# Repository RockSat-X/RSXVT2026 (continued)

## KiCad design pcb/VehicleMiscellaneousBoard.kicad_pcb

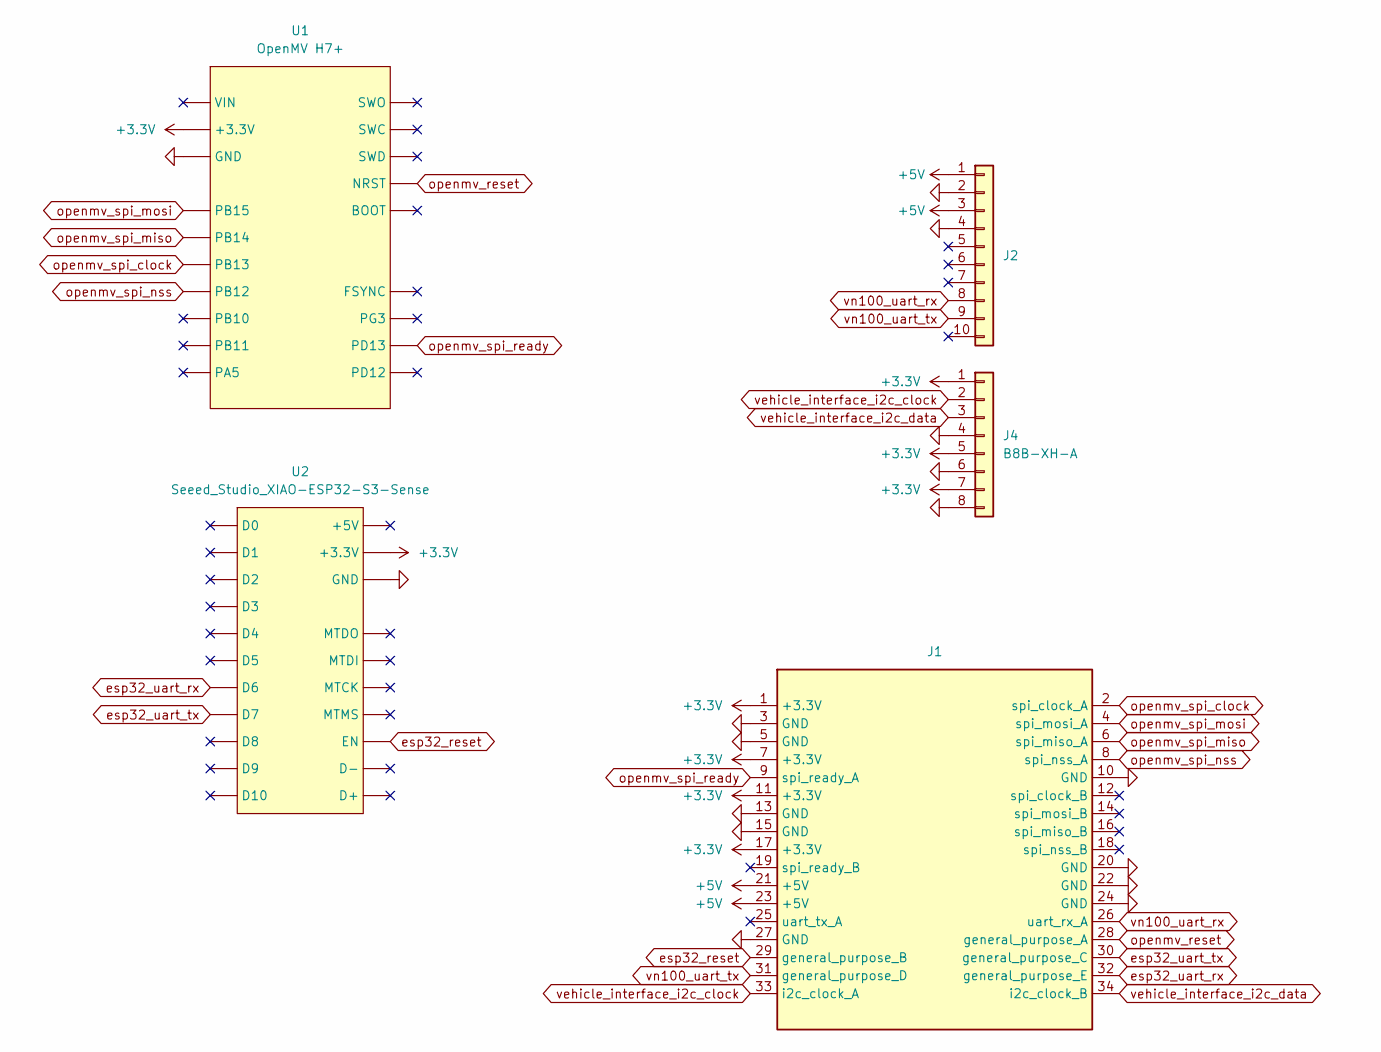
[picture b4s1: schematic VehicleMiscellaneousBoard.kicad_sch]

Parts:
J1: VehicleStackConnector
J2: Conn_02x05_Top_Bottom; JST_XH_S10B-XH-A_1x10_P2.50mm_Horizontal
J4: B8B-XH-A; JST_XH_B8B-XH-A_1x08_P2.50mm_Vertical
U1: OpenMV H7+; OpenMV_H7_Plus
U2: Seeed_Studio_XIAO-ESP32-S3-Sense; Seeed_Studio_XIAO_ESP32_S3

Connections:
+3.3V: J1.1 (+3.3V), J1.7 (+3.3V), J1.11 (+3.3V), J1.17 (+3.3V), J4.1, J4.5, J4.7, U1.+3.3V, U2.+3.3V
+5V: J1.21 (+5V), J1.23 (+5V), J2.1, J2.3
GND: J1.3 (GND), J1.5 (GND), J1.10 (GND), J1.13 (GND), J1.15 (GND), J1.20 (GND), J1.22 (GND), J1.24 (GND), J1.27 (GND), J2.2, J2.4, J4.4, J4.6, J4.8, U1.GND, U2.GND
esp32_reset: J1.29 (general_purpose_B), U2.EN
esp32_uart_rx: J1.32 (general_purpose_E), U2.D6
esp32_uart_tx: J1.30 (general_purpose_C), U2.D7
openmv_reset: J1.28 (general_purpose_A), U1.NRST
openmv_spi_clock: J1.2 (spi_clock_A), U1.PB13
openmv_spi_miso: J1.6 (spi_miso_A), U1.PB14
openmv_spi_mosi: J1.4 (spi_mosi_A), U1.PB15
openmv_spi_nss: J1.8 (spi_nss_A), U1.PB12
openmv_spi_ready: J1.9 (spi_ready_A), U1.PD13
vehicle_interface_i2c_clock: J1.33 (i2c_clock_A), J4.2
vehicle_interface_i2c_data: J1.34 (i2c_clock_B), J4.3
vn100_uart_rx: J1.26 (uart_rx_A), J2.8
vn100_uart_tx: J1.31 (general_purpose_D), J2.9

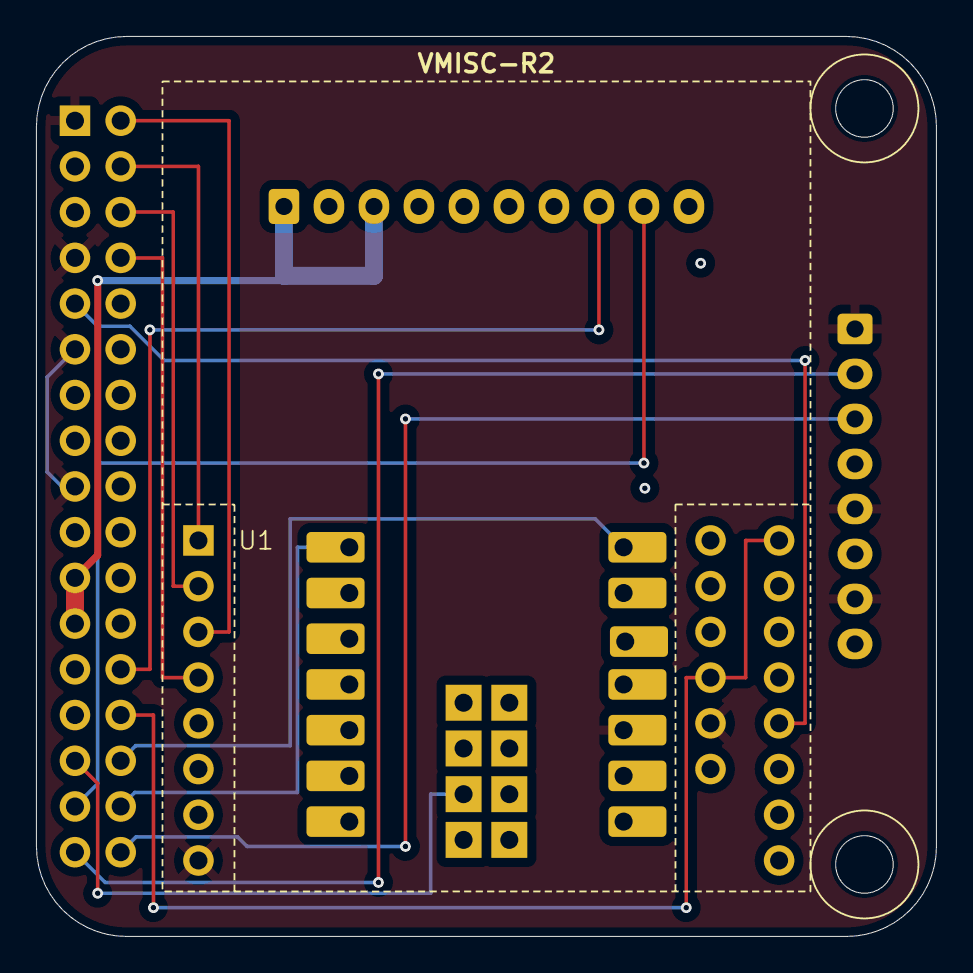
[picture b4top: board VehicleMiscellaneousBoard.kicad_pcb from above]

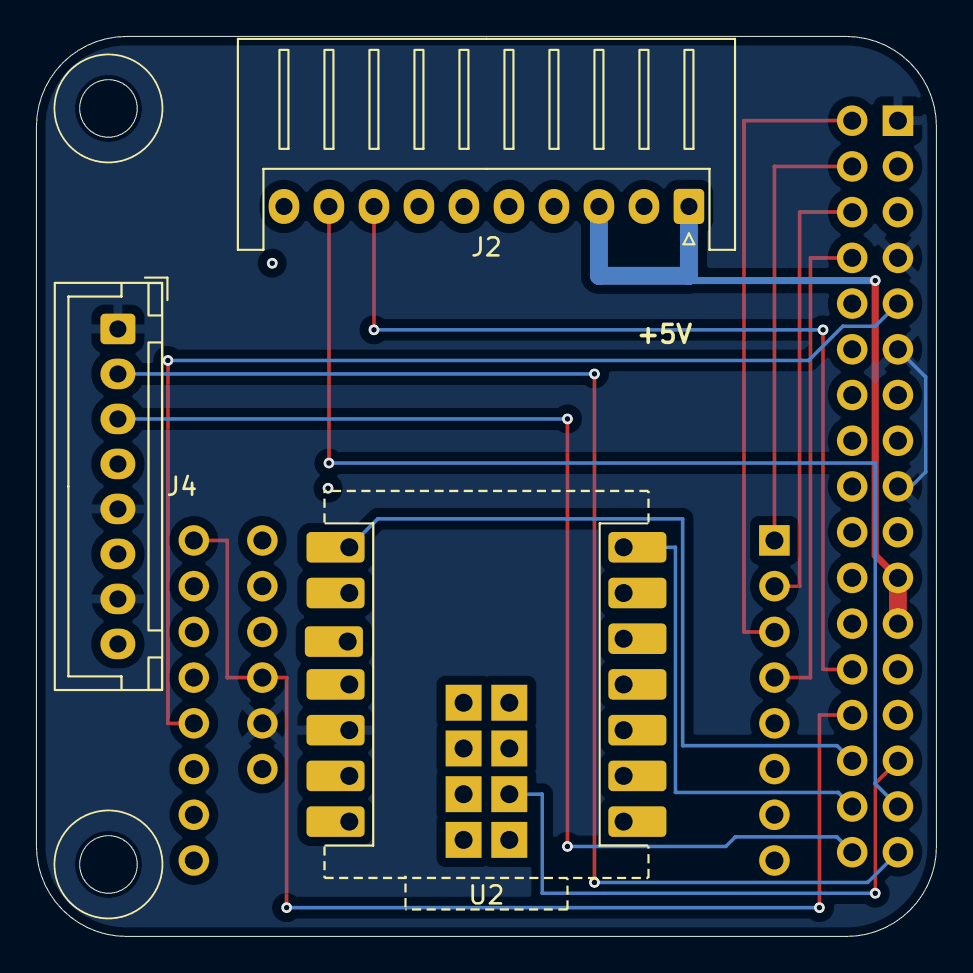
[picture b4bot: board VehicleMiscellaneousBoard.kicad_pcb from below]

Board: 4 copper layers, 50.0 x 50.0 mm, 6 parts (3 on the bottom side), 16 nets.

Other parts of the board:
N1: Housing; Dummy

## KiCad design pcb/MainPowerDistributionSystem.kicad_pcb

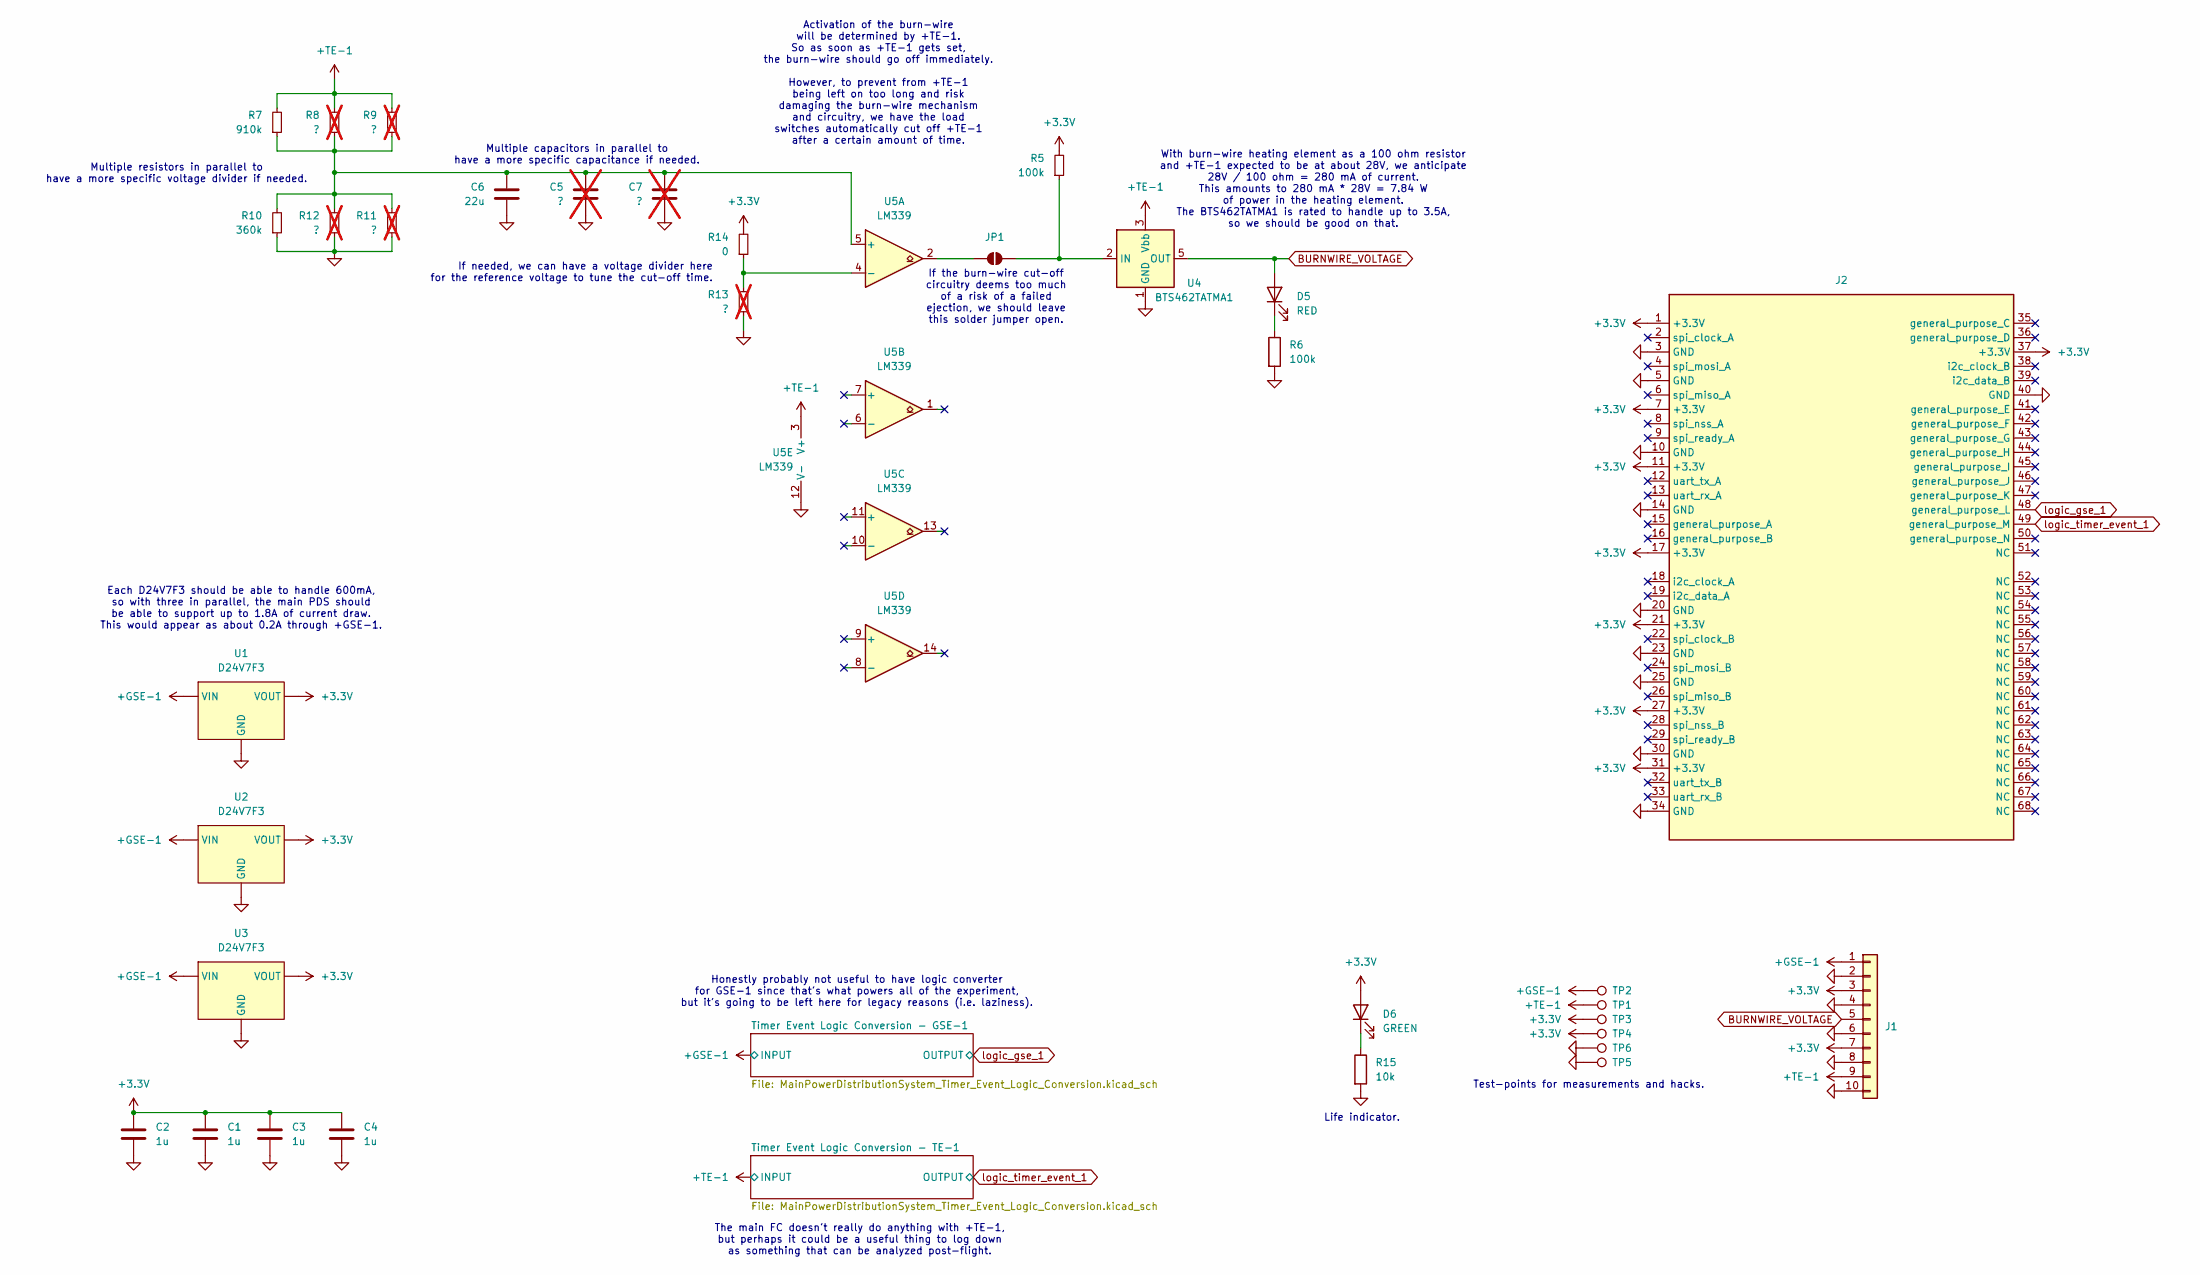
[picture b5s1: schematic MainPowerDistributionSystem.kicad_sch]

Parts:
C1, C2, C3, C4: 1u; C_1206_3216Metric_Pad1.33x1.80mm_HandSolder
C5, C7: ?; C_1206_3216Metric_Pad1.33x1.80mm_HandSolder; not fitted
C6: 22u; C_1206_3216Metric_Pad1.33x1.80mm_HandSolder
D5: RED; LED_1206_3216Metric_Pad1.42x1.75mm_HandSolder
D6: GREEN; LED_1206_3216Metric_Pad1.42x1.75mm_HandSolder
J1: Conn_02x05_Top_Bottom; JST_XH_S10B-XH-A_1x10_P2.50mm_Horizontal
J2: MainStackConnector
JP1: SolderJumper_2_Open; SolderJumper-2_P1.3mm_Open_RoundedPad1.0x1.5mm
R5, R6: 100k; R_1206_3216Metric_Pad1.30x1.75mm_HandSolder
R7: 910k; R_1206_3216Metric_Pad1.30x1.75mm_HandSolder
R8, R9, R11, R12, R13: ?; R_1206_3216Metric_Pad1.30x1.75mm_HandSolder; not fitted
R10: 360k; R_1206_3216Metric_Pad1.30x1.75mm_HandSolder
R14: 0; R_1206_3216Metric_Pad1.30x1.75mm_HandSolder
R15: 10k; R_1206_3216Metric_Pad1.30x1.75mm_HandSolder
TP1, TP2, TP3, TP4, TP5, TP6: TestPoint; TestPoint_Bridge_Pitch2.0mm_Drill0.7mm
U1, U2, U3: D24V7F3; D24V7Fx
U4: BTS462TATMA1; TO-252-4
U5: LM339; SOIC-14_3.9x8.7mm_P1.27mm

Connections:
+3.3V: C1.1, C2.1, C3.1, C4.1, D6.2 (A), J1.3, J1.7, J2.1 (+3.3V), J2.7 (+3.3V), J2.11 (+3.3V), J2.17 (+3.3V), J2.21 (+3.3V), J2.27 (+3.3V), J2.31 (+3.3V), J2.37 (+3.3V), R5.2, R14.2, TP3.1, TP4.1, U1.VOUT, U2.VOUT, U3.VOUT
+GSE-1: J1.1, TP2.1, U1.VIN, U2.VIN, U3.VIN; also elsewhere on the board
+TE-1: J1.9, R7.2, R8.2, R9.2, TP1.1, U4.3 (Vbb), U5.3 (V+); also elsewhere on the board
BURNWIRE_VOLTAGE: D5.2 (A), J1.5, U4.5 (OUT)
GND: C1.2, C2.2, C3.2, C4.2, C5.2, C6.2, C7.2, J1.2, J1.4, J1.6, J1.8, J1.10, J2.3 (GND), J2.5 (GND), J2.10 (GND), J2.14 (GND), J2.20 (GND), J2.23 (GND), J2.25 (GND), J2.30 (GND), J2.34 (GND), J2.40 (GND), R6.2, R10.1, R11.1, R12.1, R13.1, R15.2, TP5.1, TP6.1, U1.GND, U2.GND, U3.GND, U4.1 (GND), U5.12 (V-); also elsewhere on the board
unnamed: D5.1 (K), R6.1
unnamed: D6.1 (K), R15.1
unnamed: JP1.1 (A), U5.2
unnamed: JP1.2 (B), R5.1, U4.2 (IN)
unnamed: C5.1, C6.1, C7.1, R7.1, R8.1, R9.1, R10.2, R11.2, R12.2, U5.5 (+)
unnamed: R13.2, R14.1, U5.4 (-)
logic_gse_1: J2.48 (general_purpose_L); also elsewhere on the board
logic_timer_event_1: J2.49 (general_purpose_M); also elsewhere on the board

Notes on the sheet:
Multiple resistors in parallel to have a more specific voltage divider if needed.
Activation of the burn-wire will be determined by +TE-1. So as soon as +TE-1 gets set, the burn-wire should go off immediately. However, to prevent from +TE-1 being left on too long and risk damaging the burn-wire mechanism and circuitry, we have the load switches automatically cut off +TE-1 after 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
With burn-wire heating element as a 100 ohm resistor and +TE-1 expected to be at about 28V, we anticipate 28V / 100 ohm = 280 mA of current. This amounts to 280 mA * 28V = 7.84 W of power in the heating element. The BTS462TATMA1 is rated to handle up to 3.5A, so we should be good on that.
Multiple capacitors in parallel to have a more specific capacitance if needed.
If the burn-wire cut-off circuitry deems too much of a risk of a failed ejection, we should leave this solder jumper open.
Life indicator.
Honestly probably not useful to have logic converter for GSE-1 since that's what powers all of the experiment, but it's going to be left here for legacy reasons (i.e. laziness).
The main FC doesn't really do anything with +TE-1, but perhaps it could be a useful thing to log down as something that can be analyzed post-flight.
If needed, we can have a voltage divider here for the reference voltage to tune the cut-off time.
Test-points for measurements and hacks.
Each D24V7F3 should be able to handle 600mA, so with three in parallel, the main PDS should be able to support up to 1.8A of current draw. This would appear as about 0.2A through +GSE-1.

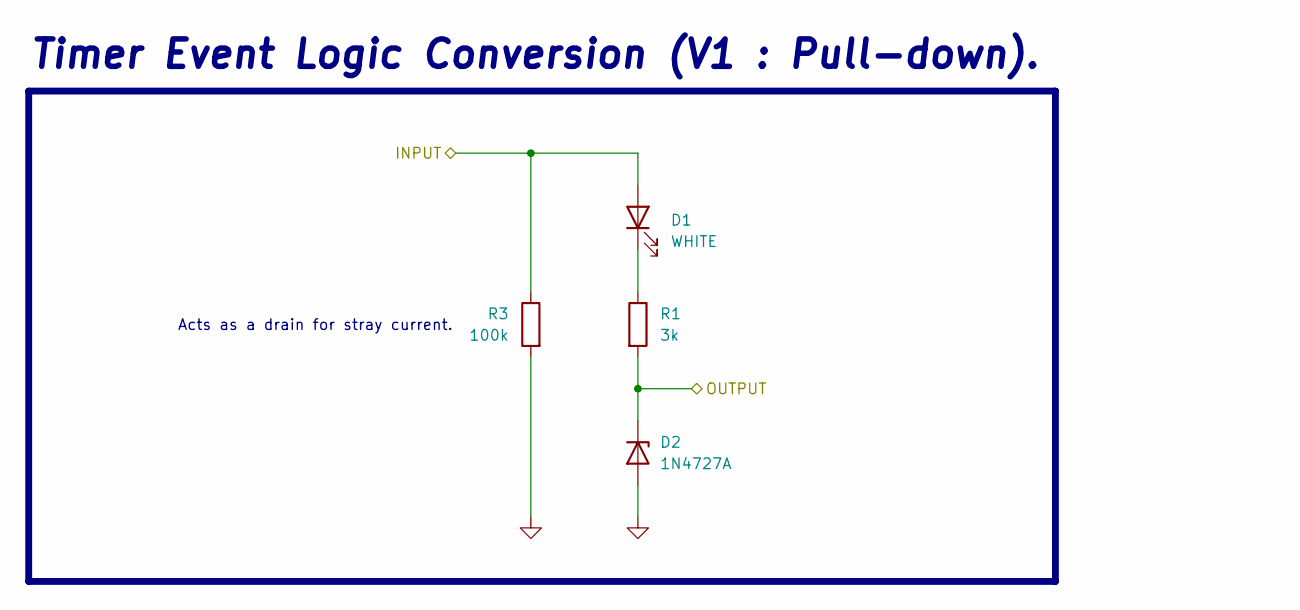
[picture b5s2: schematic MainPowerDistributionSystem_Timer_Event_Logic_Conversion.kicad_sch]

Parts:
D1: WHITE; LED_1206_3216Metric_Pad1.42x1.75mm_HandSolder
D2: 1N4727A; D_A-405_P7.62mm_Horizontal
R1: 3k; R_1206_3216Metric_Pad1.30x1.75mm_HandSolder
R3: 100k; R_1206_3216Metric_Pad1.30x1.75mm_HandSolder

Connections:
+TE-1: D1.2 (A), R3.1; also elsewhere on the board
GND: D2.2 (A), R3.2; also elsewhere on the board
unnamed: D1.1 (K), R1.1
logic_timer_event_1: D2.1 (K), R1.2; also elsewhere on the board

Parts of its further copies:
D3: WHITE; LED_1206_3216Metric_Pad1.42x1.75mm_HandSolder
D4: 1N4727A; D_A-405_P7.62mm_Horizontal
R2: 3k; R_1206_3216Metric_Pad1.30x1.75mm_HandSolder
R4: 100k; R_1206_3216Metric_Pad1.30x1.75mm_HandSolder

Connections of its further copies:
+GSE-1: D3.2 (A), R4.1; also elsewhere on the board
GND: D4.2 (A), R4.2; also elsewhere on the board
unnamed: D3.1 (K), R2.1
logic_gse_1: D4.1 (K), R2.2; also elsewhere on the board

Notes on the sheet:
Timer Event Logic Conversion (V1 : Pull-down).
Acts as a drain for stray current.

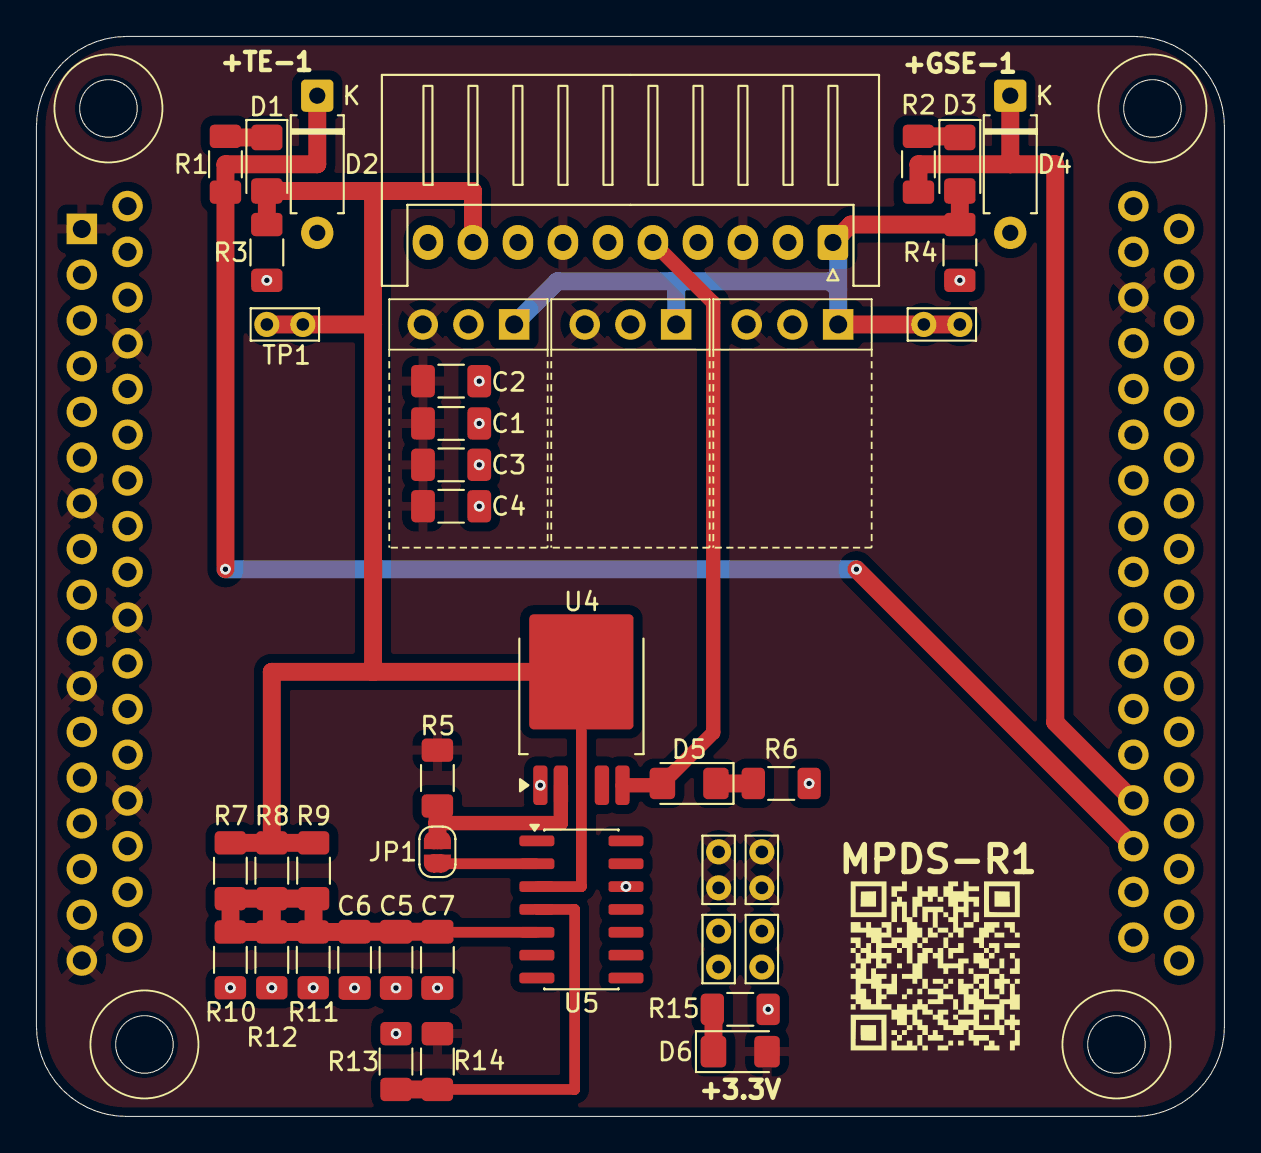
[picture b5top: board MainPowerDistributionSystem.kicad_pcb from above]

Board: 2 copper layers, 66.0 x 60.0 mm, 43 parts (0 on the bottom side), 15 nets.

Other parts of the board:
N1: Housing; MainPowerDistributionSystemHousing

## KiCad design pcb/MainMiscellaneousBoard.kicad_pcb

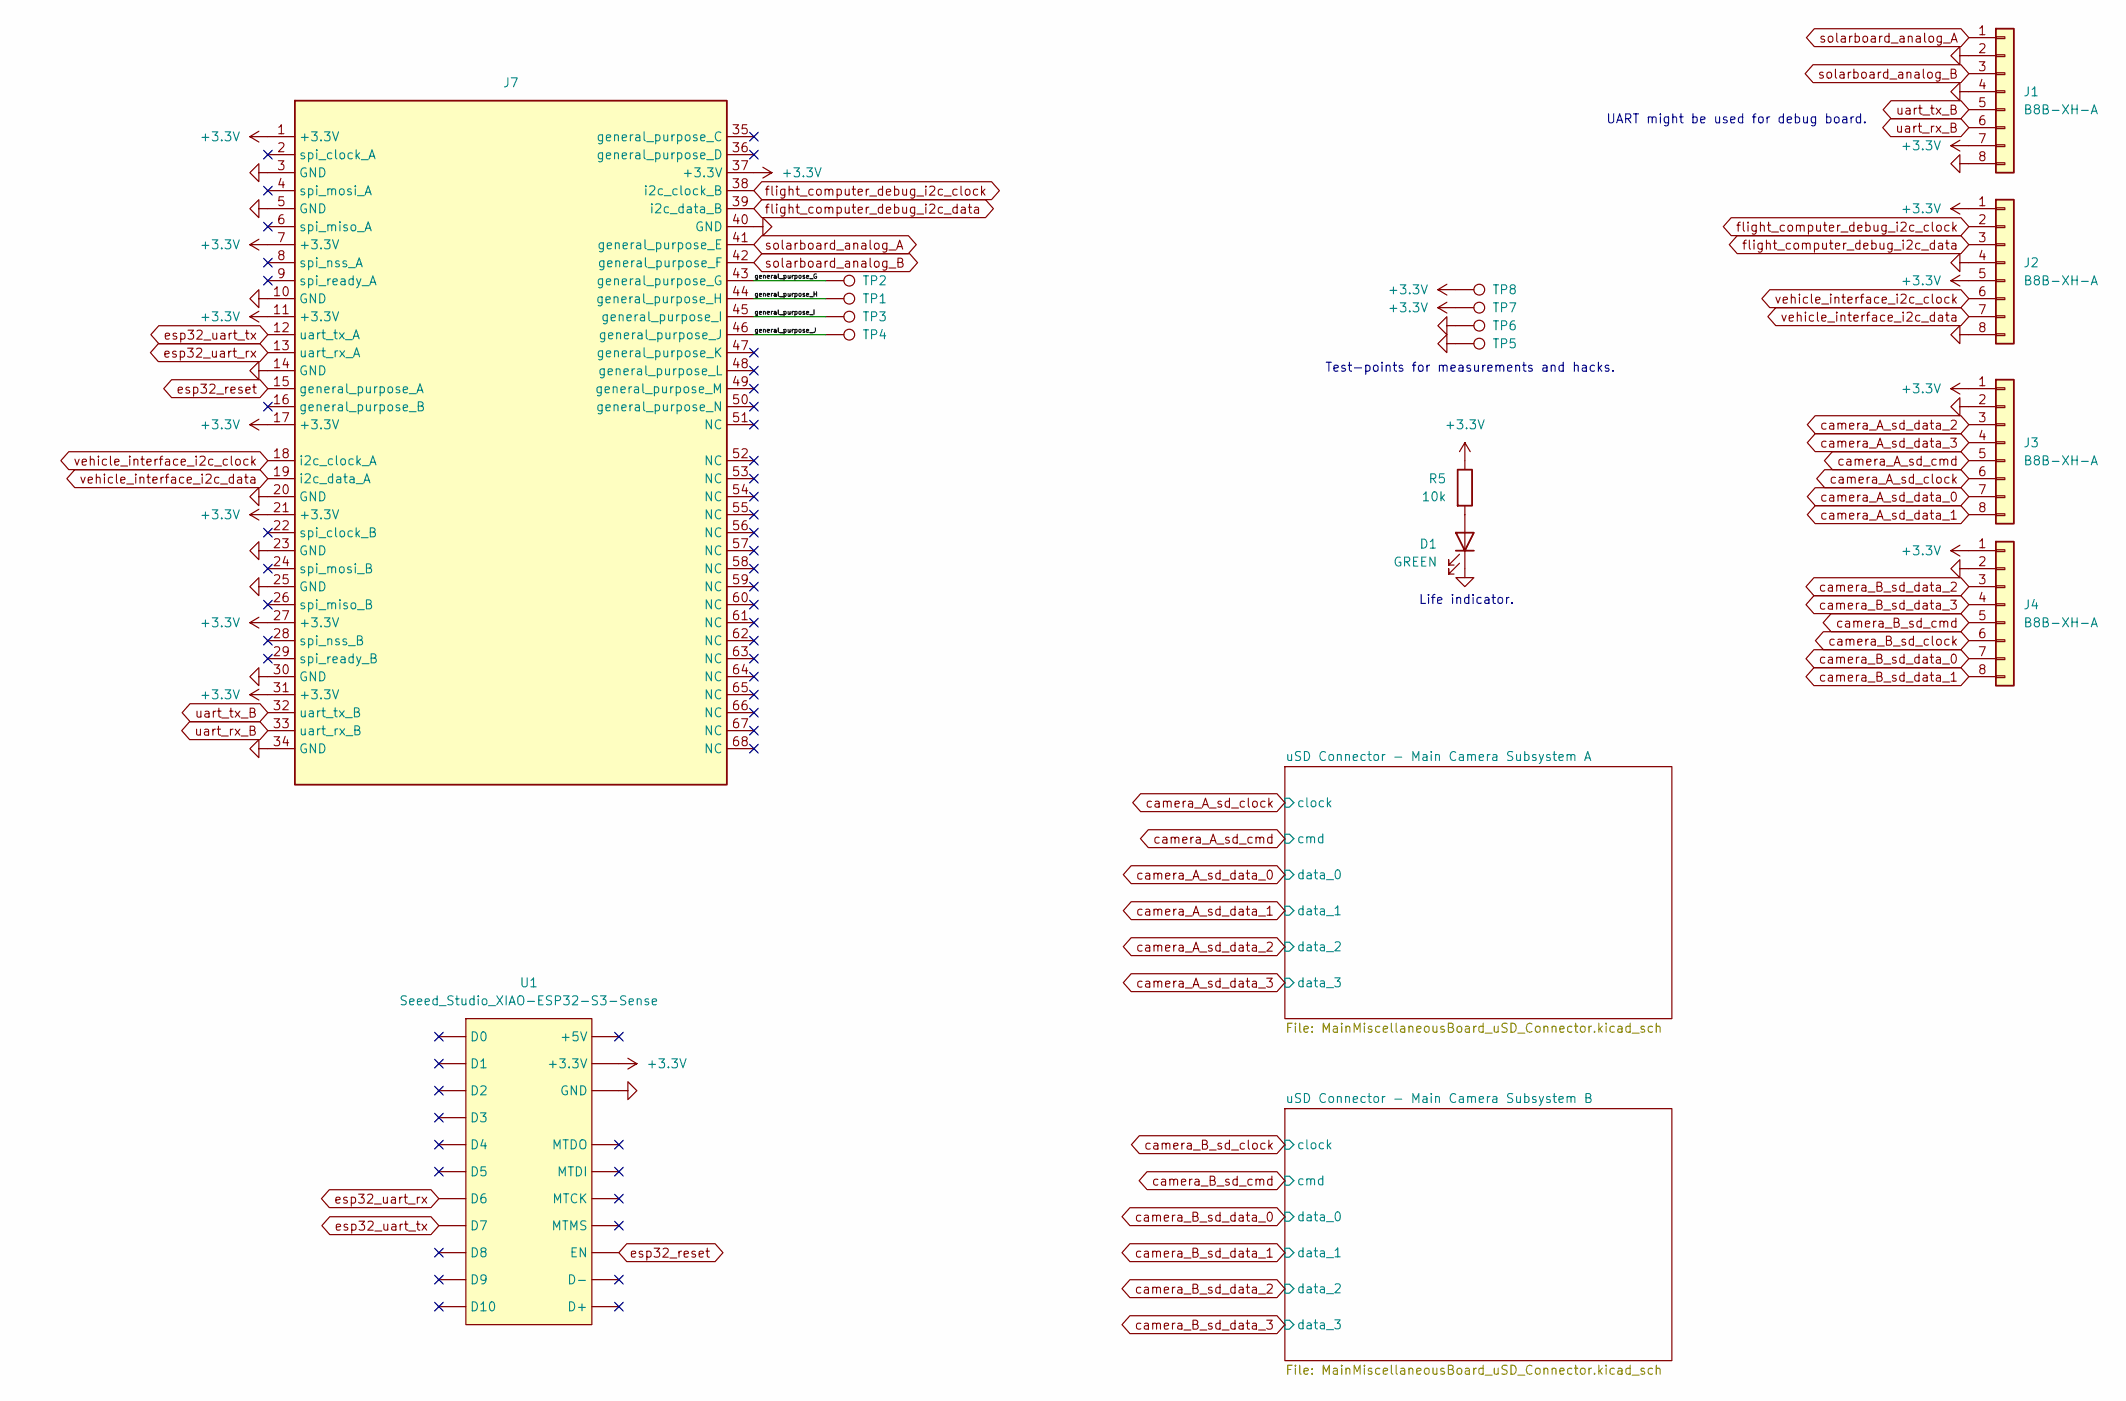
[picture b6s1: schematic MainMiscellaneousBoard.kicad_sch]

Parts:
D1: GREEN; LED_1206_3216Metric_Pad1.42x1.75mm_HandSolder
J1, J2, J3, J4: B8B-XH-A; JST_XH_B8B-XH-A_1x08_P2.50mm_Vertical
J7: MainStackConnector
R5: 10k; R_1206_3216Metric_Pad1.30x1.75mm_HandSolder
TP1, TP2, TP3, TP4, TP5, TP6, TP7, TP8: TestPoint; TestPoint_Bridge_Pitch2.0mm_Drill0.7mm
U1: Seeed_Studio_XIAO-ESP32-S3-Sense; Seeed_Studio_XIAO_ESP32_S3

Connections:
+3.3V: J1.7, J2.1, J2.5, J3.1, J4.1, J7.1 (+3.3V), J7.7 (+3.3V), J7.11 (+3.3V), J7.17 (+3.3V), J7.21 (+3.3V), J7.27 (+3.3V), J7.31 (+3.3V), J7.37 (+3.3V), R5.1, TP7.1, TP8.1, U1.+3.3V; also elsewhere on the board
/general_purpose_G: J7.43 (general_purpose_G), TP2.1
/general_purpose_H: J7.44 (general_purpose_H), TP1.1
/general_purpose_I: J7.45 (general_purpose_I), TP3.1
/general_purpose_J: J7.46 (general_purpose_J), TP4.1
GND: D1.1 (K), J1.2, J1.4, J1.8, J2.4, J2.8, J3.2, J4.2, J7.3 (GND), J7.5 (GND), J7.10 (GND), J7.14 (GND), J7.20 (GND), J7.23 (GND), J7.25 (GND), J7.30 (GND), J7.34 (GND), J7.40 (GND), TP5.1, TP6.1, U1.GND; also elsewhere on the board
unnamed: D1.2 (A), R5.2
camera_A_sd_clock: J3.6; also elsewhere on the board
camera_A_sd_cmd: J3.5; also elsewhere on the board
camera_A_sd_data_0: J3.7; also elsewhere on the board
camera_A_sd_data_1: J3.8; also elsewhere on the board
camera_A_sd_data_2: J3.3; also elsewhere on the board
camera_A_sd_data_3: J3.4; also elsewhere on the board
camera_B_sd_clock: J4.6; also elsewhere on the board
camera_B_sd_cmd: J4.5; also elsewhere on the board
camera_B_sd_data_0: J4.7; also elsewhere on the board
camera_B_sd_data_1: J4.8; also elsewhere on the board
camera_B_sd_data_2: J4.3; also elsewhere on the board
camera_B_sd_data_3: J4.4; also elsewhere on the board
esp32_reset: J7.15 (general_purpose_A), U1.EN
esp32_uart_rx: J7.13 (uart_rx_A), U1.D6
esp32_uart_tx: J7.12 (uart_tx_A), U1.D7
flight_computer_debug_i2c_clock: J2.2, J7.38 (i2c_clock_B)
flight_computer_debug_i2c_data: J2.3, J7.39 (i2c_data_B)
solarboard_analog_A: J1.1, J7.41 (general_purpose_E)
solarboard_analog_B: J1.3, J7.42 (general_purpose_F)
uart_rx_B: J1.6, J7.33 (uart_rx_B)
uart_tx_B: J1.5, J7.32 (uart_tx_B)
vehicle_interface_i2c_clock: J2.6, J7.18 (i2c_clock_A)
vehicle_interface_i2c_data: J2.7, J7.19 (i2c_data_A)

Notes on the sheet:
Test-points for measurements and hacks.
Life indicator.
UART might be used for debug board.

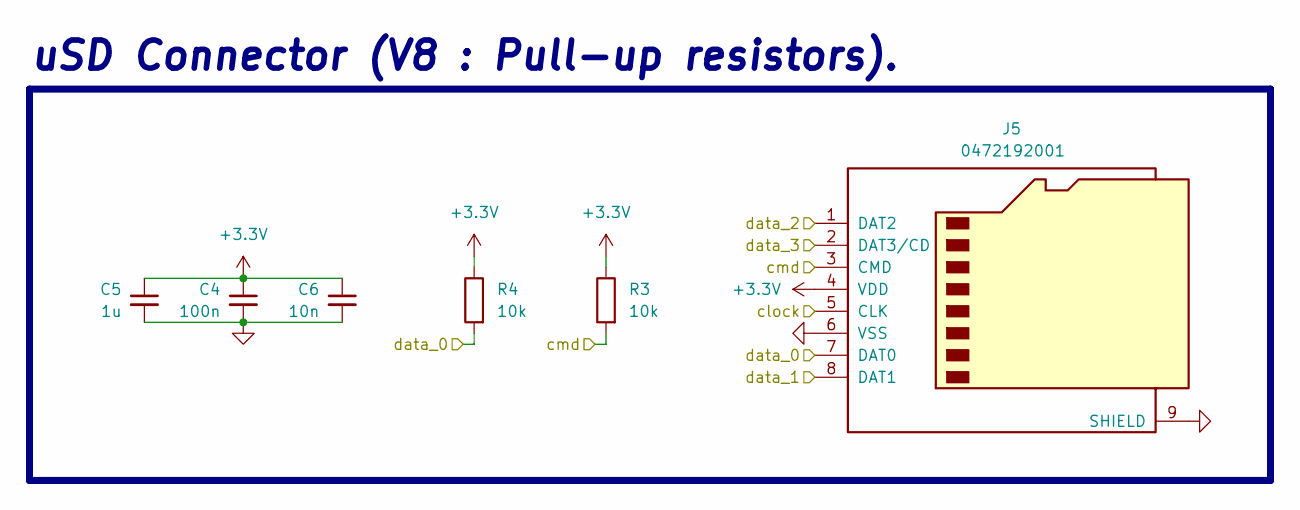
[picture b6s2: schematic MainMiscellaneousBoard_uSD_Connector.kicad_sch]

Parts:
C4: 100n; C_1206_3216Metric_Pad1.33x1.80mm_HandSolder
C5: 1u; C_1206_3216Metric_Pad1.33x1.80mm_HandSolder
C6: 10n; C_1206_3216Metric_Pad1.33x1.80mm_HandSolder
J5: 0472192001; microSD_HC_Molex_47219-2001
R3, R4: 10k; R_1206_3216Metric_Pad1.30x1.75mm_HandSolder

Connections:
+3.3V: C4.1, C5.1, C6.1, J5.4 (VDD), R3.1, R4.1; also elsewhere on the board
GND: C4.2, C5.2, C6.2, J5.6 (VSS), J5.9 (SHIELD); also elsewhere on the board
camera_A_sd_clock: J5.5 (CLK); also elsewhere on the board
camera_A_sd_cmd: J5.3 (CMD), R3.2; also elsewhere on the board
camera_A_sd_data_0: J5.7 (DAT0), R4.2; also elsewhere on the board
camera_A_sd_data_1: J5.8 (DAT1); also elsewhere on the board
camera_A_sd_data_2: J5.1 (DAT2); also elsewhere on the board
camera_A_sd_data_3: J5.2 (DAT3/CD); also elsewhere on the board

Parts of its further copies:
C1: 1u; C_1206_3216Metric_Pad1.33x1.80mm_HandSolder
C2: 100n; C_1206_3216Metric_Pad1.33x1.80mm_HandSolder
C3: 10n; C_1206_3216Metric_Pad1.33x1.80mm_HandSolder
J6: 0472192001; microSD_HC_Molex_47219-2001
R1, R2: 10k; R_1206_3216Metric_Pad1.30x1.75mm_HandSolder

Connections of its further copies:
+3.3V: C1.1, C2.1, C3.1, J6.4 (VDD), R1.1, R2.1; also elsewhere on the board
GND: C1.2, C2.2, C3.2, J6.6 (VSS), J6.9 (SHIELD); also elsewhere on the board
camera_B_sd_clock: J6.5 (CLK); also elsewhere on the board
camera_B_sd_cmd: J6.3 (CMD), R2.2; also elsewhere on the board
camera_B_sd_data_0: J6.7 (DAT0), R1.2; also elsewhere on the board
camera_B_sd_data_1: J6.8 (DAT1); also elsewhere on the board
camera_B_sd_data_2: J6.1 (DAT2); also elsewhere on the board
camera_B_sd_data_3: J6.2 (DAT3/CD); also elsewhere on the board

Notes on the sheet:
uSD Connector (V8 : Pull-up resistors).

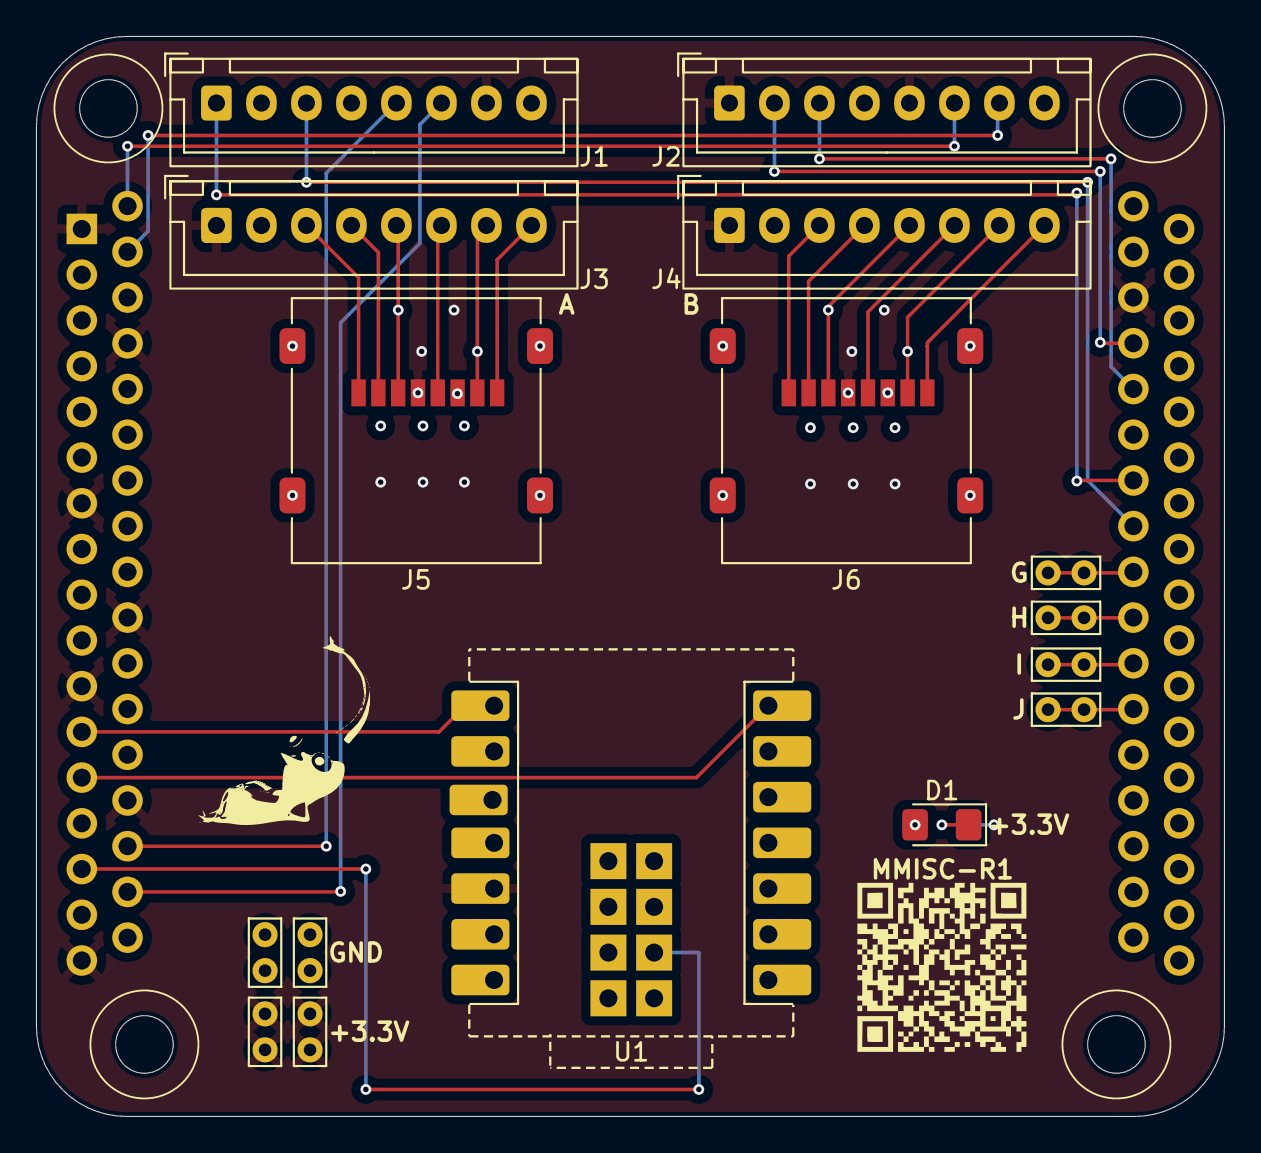
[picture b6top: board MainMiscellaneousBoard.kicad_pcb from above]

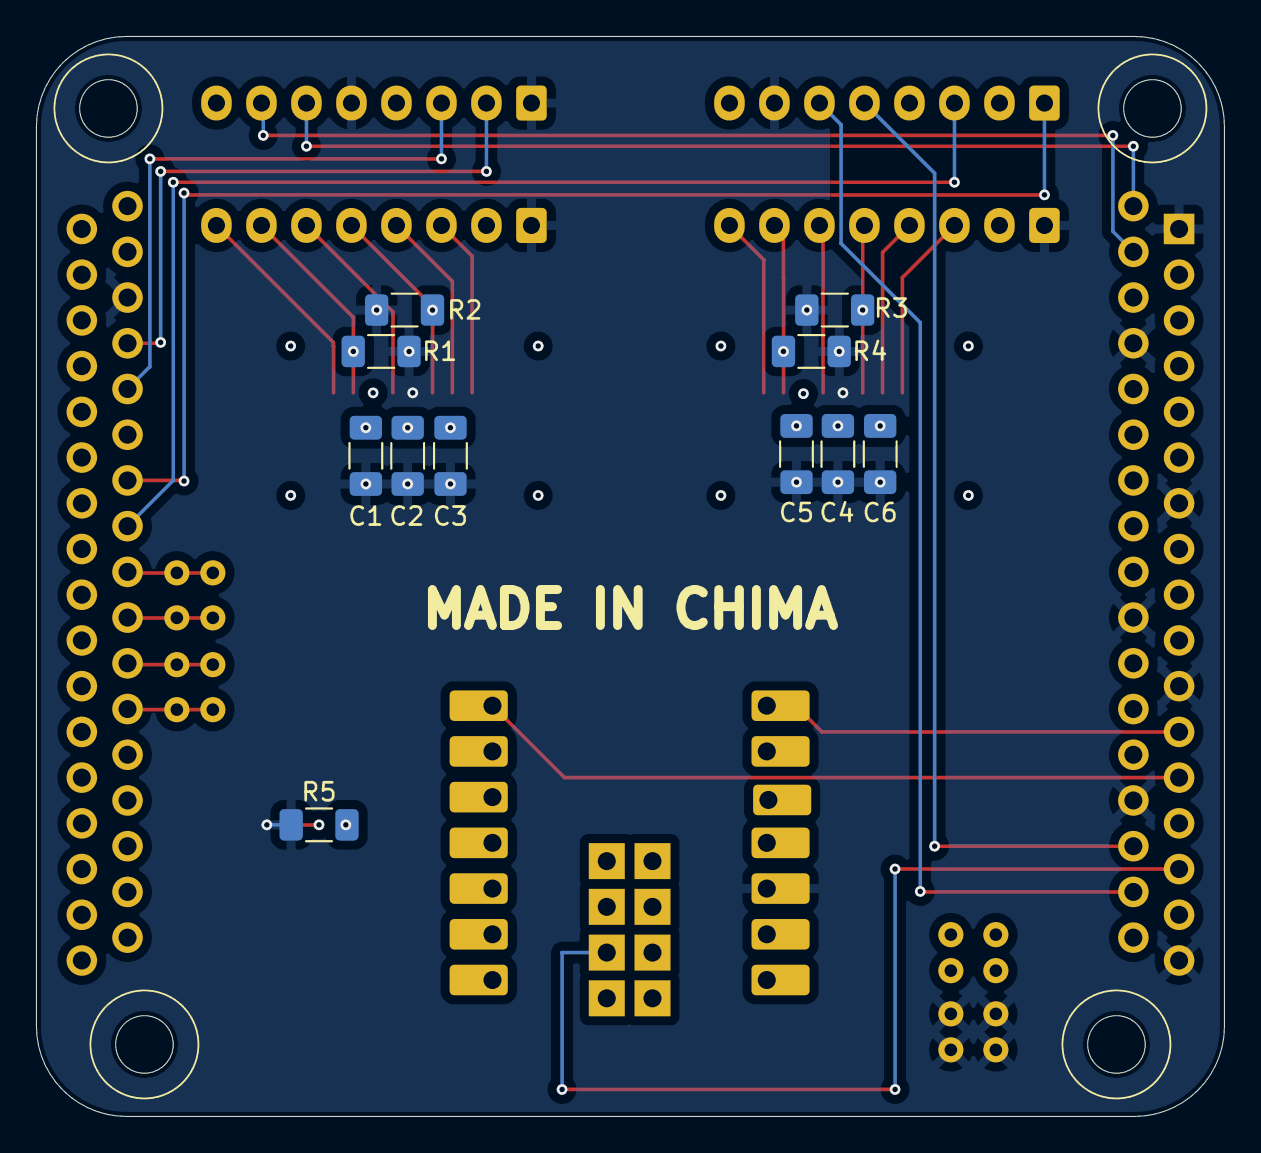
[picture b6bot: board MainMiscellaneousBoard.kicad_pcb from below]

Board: 4 copper layers, 66.0 x 60.0 mm, 29 parts (11 on the bottom side), 30 nets.

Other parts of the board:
N1: Housing; MainMiscellaneousBoardHousing
